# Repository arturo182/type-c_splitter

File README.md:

# USB Type-C Host Power and Data Splitter

This board allows you to provide external power to a USB Host (and Device).

There is no PD, 5V only.

It's a bit cursed.

And untested.

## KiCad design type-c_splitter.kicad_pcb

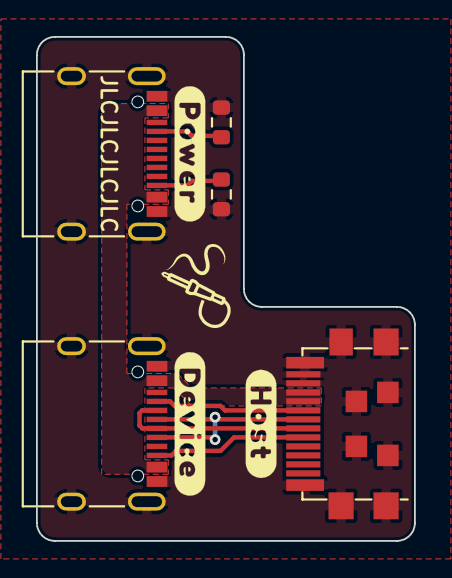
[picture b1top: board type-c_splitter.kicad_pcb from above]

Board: 2 copper layers, 21.0 x 28.0 mm, 5 parts (0 on the bottom side), 8 nets.

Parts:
J1: Power; USB_C_Receptacle_XKB_U262-16XN-4BVC11
J2: Data; USB_C_Receptacle_XKB_U262-16XN-4BVC11
P1: Plug; USB_C_Plug_UTC009-C12
R1, R2: 5.1K; R_0603_1608Metric

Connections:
GND: J1.A1 (GND), J1.A12 (GND), J1.B1 (GND), J1.B12 (GND), J1.S1 (SHIELD), J2.A1 (GND), J2.A12 (GND), J2.B1 (GND), J2.B12 (GND), J2.S1 (SHIELD), P1.A1 (GND), P1.B12 (GND), P1.S1 (SHIELD), R1.2, R2.2
unnamed: J1.A5 (CC1), R1.1
unnamed: J1.B5 (CC2), R2.1
unnamed: J2.A5 (CC1), P1.A5 (CC)
unnamed: J2.A6 (D+), J2.B6 (D+), P1.A6 (D+)
unnamed: J2.A7 (D-), J2.B7 (D-), P1.A7 (D-)
unnamed: J2.B5 (CC2), P1.B5 (VCONN)
VBUS: J1.A4 (VBUS), J1.A9 (VBUS), J1.B4 (VBUS), J1.B9 (VBUS), J2.A4 (VBUS), J2.A9 (VBUS), J2.B4 (VBUS), J2.B9 (VBUS), P1.A4 (VBUS), P1.B9 (VBUS)

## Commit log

2021-02-09 Initial import
2021-02-09 Add pdf and step
2021-02-09 Add JLCJLCJLCJLC
